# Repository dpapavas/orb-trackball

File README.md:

<!-- -*- coding: utf-8 -*- -->

# The Orb trackball

The Orb is a parametric trackball design, which uses BTUs as bearings to support
the ball for smooth, accurate, low-maintenance operation.  The design has the
form of a Scheme program, meant to be executed using the
[Gamma](https://github.com/dpapavas/gamma) computational geometry compiler, in
order to produce model files, that can then be used for fabrication.  This
allows substantial configurability, since parameters of the program can be
changed in order to alter the design, for instance to change the trackball
diameter, or adapt the design to different BTU part.

The Orb was created as a relatively complex application, that could be used to
drive the design of Gamma during the initial stages of development, but it works
pretty well and can be used in practice as a pointing device.  For a frew more
photos, see the [doc/](./doc) directory and see below for building instructions,
if you're interested in making one.

## Building an Orb

These instructions will be rather brief, as I do not expect many people to be
interested in making an Orb.  If you find that you are though and are unclear
about something, please open an issue on the Github project page, requesting
better documentation, making sure to mention the details you're unclear about.

The default configuration is made for a 55mm trackball (such as the one used in
the Kensington Expert Mouse) and the Ahcell D-6H BTU.  The PCB is mounted with
M3 screws, using threaded inserts with an M5-0.5x12 outer thread. If you decide
to use the same parts, you can use the pre-built STLs in [things/](./things/) and
skip the next section.

### Making design changes

To adapt the design for different parts (or make other customizations), you'll
first have to install Gamma. See its [project
page](https://github.com/dpapavas/gamma), for further instructions.  Once that
is accomplished, you're ready to compile the design.  The compilation process
creates lots of files, as it caches all intermediate non-trivial computations,
so it's best to carry it out in a separate directory, to keep things tidy.  (The
commands below assume you're starting out at the top-level directory of the Orb
sources.)

```bash
$ mkdir build
$ cd build
```

The design source (located in the [scheme/](./scheme/) directory) defines a set
of outputs, each of which can be compiled and written to a file in one of the
supported output formats.  To see the available outputs, you can use the
`-Woutputs` option, which enables warnings about unused outputs.  This will list
all of them, since we haven't selected any.

```bash
gamma -Woutputs ../scheme/trackball.scm
```

You can examine the sources to see what all of these outputs are about.  To
compile designs with the default configuration, we'll only need the `chassis` ,
`boot` and `cap` outputs, and we'll only need to concern ourselves with the
first for the time being.  We'll first build a draft design (`-Ddraft`), since
compilation in full resolution can take quite long and we just want to change a
few parameters and get an idea of the result.

```bash
gamma -Ddraft -o chassis.stl ../scheme/trackball.scm
```

The first compilation will typically take a while.  In draft mode, it should be
several minutes.  If you're worried that Gamma has frozen, you can use the
`--dump-operations=-` option, to convince yourself otherwise.  It takes so long,
because all calculations need to be carried out from scratch, but this will
typically only happen once.  Intermediate results are saved (which explains the
slew of `.o` or `.zo` files which now exist in your build directory) and future
recompilations will only recalculate the parts that have changed.  This helps
keep compilation times at relatively interactive levels most of the time.

To change the design to accept a different size ball, say a pool ball with a
diameter of 57.15mm, you only need to change the definition `ball-radius`
(setting it to `5715/200` [^1]) and recompile as before.  (You may note that
this compilation again takes some time.  That is because the change is quite
fundamental and requires changes and thus recalculation of most of the
geometry.)

Adapting the design to a different BTU part is also relatively straightforward.
For instance, if you want to use the `11MI-05-13` part (made by various
manufacturers) you need only to change `btu-radius` to `13/2` and
`btu-thread-length` to `15`.

After inspecting the draft result for any obvious defects, it's time to compile
the final part.  We work as before, but remove the `-Ddraft` option.

```bash
gamma -o chassis.stl ../scheme/trackball.scm
```

The part looks okay, but we can be more thorough.  The `interference` output takes
the intersection of the main chassis part with all mounted peripherals (PCB
board, BTUs, ball, etc.).  The result should ideally be empty, otherwise there
will be interference during assembly, but in practice, very small intersection
can be okay, depending on manufacturing tolerances and intended postprocessing of
the part.

We can also use the `-Dvertical=...` and `-Dhorizontal=...` options, to inspect
cross-sections of the part, for instance to make sure that wall thicknesses are
acceptable at critical points.  (See the comments in the sources for more
details.)

To get an idea of the assembled device, we just have to select the `assembly`
output and define some options to specify what to include in the assembly.

```bash
gamma -Dplace-ball -Dplace-board -Dplace-bearings -Dplace-caps -Dplace-boot -o assembly.stl ../scheme/trackball.scm
```

Finally, to make the bottom cover and keycaps, use the `boot` and `cap` outputs.

```bash
gamma -o boot.stl -o cap.stl ../scheme/trackball.scm
```

All this is not meant to give the idea that the design is infinitely flexible;
there are limits to the changes that can be carried out through simple
reparameterization.  These limits generally depend on the design, which can be
made to be more or less "generic", but small changes are usually okay.  After a
point though, changes in one part of the design may necessitate changes in other
parameters to ensure a defect-free result and still larger alterations can well
require changes to the design itself.

For some more tips on using Gamma, see the documentation for the [examples in
its project page](https://github.com/dpapavas/gamma/tree/master/examples).

## Fabrication

Once the parts have been compiled, they can be fabricated using a 3D printer, a
prototype fabrication service, or any other means at your disposal.  Note that,
depending on the manufacturing tolerance of the chosen method, you may need to
make minor changes to some design parameters to ensure perfect fit.
Alternatively, you can also postprocess the part instead.

The main chassis part and keycaps should be made in plastic (for instance using
TPU 3D printing filament) while the boot is meant to be flexible (TPU filament
or any rubber-like material should work fine).

## The controller board

The controller PCB was designed with [KiCad 6.0.7](https://kicad.org/)
and all relevant files are contained in the [kicad/](./kicad)
directory.

There are numerous fabrication services, where you can simply upload the KiCad
PCB file ([kicad/keyboard_mcu.kicad_pcb](./kicad/keyboard_mcu.kicad_pcb)) and
have a small number of PCBs fabricated and sent to you at a small price.  One
example, that is simple to use as it doesn't present you with a bewildering
array of choices, is [OSH Park](https://oshpark.com/).  Other services might
require so-called Gerber files, an industry standard which
[KiCad](https://kicad.org/) can generate.

The controller is designed around the Pixart PMW3389DM-T3QU optical sensor and
supports up to 5 buttons (or potentially 6, if some sort of matrix circuit is
used).  It should be adaptable to the PMW3360DM‐T2QU part, which is pin
compatible and uses the same lens, but note that some components will have to be
changed (for instance the current limiting resistor for the sensor LED).

### BOM

Apart from the PCBs, you'll also need the following parts:

| Component(s) | Part description | Part # |
| ------------ | ---------------- | ------ |
| C1, C14, C15, C18 (4 pcs, 10uF) | 10uF, 10%, X7R, 0603 | GRM188Z71A106KA73D |
| C2, C3 (2 pcs, 22p) | 15PF, 1%, C0G (NP0), 0603 | GRM1885C1H150FA01D |
| C4, C6, C7, C8, C10, C11, C12, C20 (8 pcs, 100nF) | 0.1uF, 10%, X7R, 0603 | EMK107B7104KA-T |
| C5, C9, C16, C17, C19 (5 pcs, 1uF) | 1uF, 10%, X7R, 0603 | EMK107B7105KA-T |
| C13 (1 pcs, 4.7uF 10V) | 4.7uF, 10V, 10%, X5R, 0603 | LMK107BJ475KA-T |
| J1 (1 pcs, USB_B_Micro) | USB Micro Type B connector | Wurth 629105150521 |
| J2, J3 (2 pcs, Conn) | 2.0mm pin header | Harwin M22-2530305 |
|  | 2.0mm female housing | Harwin M22-3010300 |
|  | 2.0mm crimp contact | Harwin M22-3040042 |
| R1, R2 (2 pcs, 22) | 22Ω, 1%, 0603 | CRCW060322R0FKEA |
| R3, R6 (2 pcs, 10K) | 10kΩ, 1%, 0603 | CRCW060310K0FKEA |
| R4 (1 pcs, 1k) | 1kΩ, 1%, 0603 | RCA06031K00FKEA |
| R5 (1 pcs, 13) | 13Ω, 1%, 0603 | CRCW060313R0FKEA |
| SW1 (1 pcs, SW_Push) | Tactile Switch SPST-NO | TL3305AF160QG |
| U1 (1 pcs ATmega32U4-AU) | AVR microcontroller | ATMEGA32U4-AU |
| U2 (1 pcs, LD39015M33R) | 150mA voltage regulator, 3.3V, SOT-23-5 | LD39015M33R |
| U3 (1 pcs, PMW3389-T3QU) | Optical sensor chip | PMW3389-T3QU |
| | Optical sensor lens | LM19‐LSI |
| U4 (1 pcs, TLV70019_SOT23-5) | 200mA voltage regulator, 1.9V, SOT-23-5 | TLV70019DDCR |
| Y1 (1 pcs, Crystal_GND24) | Four pin crystal, GND on pins 2 and 4 | ABM3B-8.000MHZ-10-1-U-T |

I've tried to select components with high availability, but you can treat the
part numbers given for the two-terminal chip resistor and capacitors as
suggestions.  Any part with the specifications listed in the part description
should do equally well.

In addition to the above, you'll need 5 Kailh CPG1350 CHOC low profile switches.
You can find these in many variations, but I would recommend low actuation force
parts, such as the "Red Rro" linear, or "Blue" clicky versions.  Apart from
ergonomic considerations, since the force of actuation is transmitted radially
to the chassis, it will tend to shift it around on the desk if it is too high.

Finally, I would advise not crimping your own wires unless you have the proper
equipment, prior experience and know you can do a good job.  The procedure can
be rather tedious and getting a proper result can be hard to impossible,
depending on the tools used.  You can get pre-crimped wires instead, but if you
do decide to crimp your own, get *plenty* of crimp terminals.

## Assembly

Assembly is simple in theory, but it can get tricky due to the confined work
space.  Start by inserting the threaded inserts.  The default design takes
inserts for M3 screws, with M5-0.5x12 outer thread, but it can be adapted to
other parts, if necessary (through the `board-insert-thread` and `boss-radius`
parameters).  See
[here](https://github.com/dpapavas/lagrange-keyboard/blob/master/BUILD.md#installing-the-threaded-inserts)
for installation instructions.

Continue by creating a common ground bus for the switches.  One way, is to make
it out of a single solid core wire with exposed loops at the proper intervals,
that can be soldered onto one terminal of each switch.  See
[here](https://github.com/dpapavas/lagrange-keyboard/blob/master/BUILD.md#rows)
for a potential technique.  The wire should have some slack, so that you can
pull the loops one at a time, far enough out of the switch hole, in order to
solder it to the switch, but not too much slack, or else the wire might
interfere with other parts.

Continue with the crimped and terminated wires for the switches.  These should
initially be of ample length, so that they can be threaded through the wiring
guides (the loops around the lens mating surface), around the lens and through
the switch holes (one pair through each hole, plus one common ground wire
connected to the ground bus), with the terminals at the place where the mating
headers on the board will end up.  Again, leave some slack, so that you can mate
the headers during assembly, but not too much, then cut the wires to length and
solder them, one at a time, to the switches and ground bus.

Carefully remove the Kapton tape protecting the optics of the sensor chip making
sure to hold the PCB with the chip face down, to avoid getting any dust on the
exposed optics, then quickly insert the lens (practice a bit before removing the
tape, to get the hang of the process).  Insert the PCB-lens assembly far enough
into the chassis to attach the headers, then insert it fully, making sure that
no wiring has been caught between the PCB or lens and the mating sites on the
chassis and fasten it using M3x12 button head screws.  Finally insert the boot
and you're done.

Unless the boot is manufactured using a high grip material, it is very much
recommended to coat the bottom with some silicone, or similar material, to
ensure sufficient traction and keep the device from sliding around.

## Firmware

Before building the firmware, have a look at the `./src/config.h` header and
make any necessary configuration changes.  You're probably going to have to set
the button pins, unless you happened to used the same pinout as I, but you can
also change the device-to-OS button mapping, optical resolution, sensitivities,
etc.

To build the firmware, you'll need the AVR GCC toolchain, which you can most
likely install through your system's package system.  Then building can be done
simply by:

```bash
$ cd src
$ make
```

Assuming nothing has gone wrong, connect the device to your computer and press
the reset switch.  You can then install the firmware with:

```bash
$ make install
```

## License

The Scheme code in [scheme/](./scheme), producing the Orb's designs, is
distributed under the [GNU Affero General Public License Version
3](./LICENSE.AGPL).

The firmware sources in [src/](./src), except for the portion in the
[src/LUFA/](./src/LUFA/) directory, as well as the controller PCB design
residing in [kicad/](./kicad/), is distributed under the [GNU General
Public License Version 3](./LICENSE.GPL).

For the sources in the [src/LUFA/](./src/LUFA/) see the [license
notice](./src/LUFA/License.txt) therein.

[^1]: You could also set it to `28.575` and it would work fine, but rational
      numbers should probably be preferred.  Gamma works with exact arithmetic
      on rational numbers (for the most part), so using floating point-input can
      result in needlessly "large" numbers.  For instance `28.575` is really
      `28.575000762939453125` in double precision floating point, with a
      rational representation of `8043147459506995/281474976710656`, instead of
      the much simpler `5715/200`.  (There's technically also some loss of
      precision, but this is generally down at the atomic scale, so we can
      probably ignore it).

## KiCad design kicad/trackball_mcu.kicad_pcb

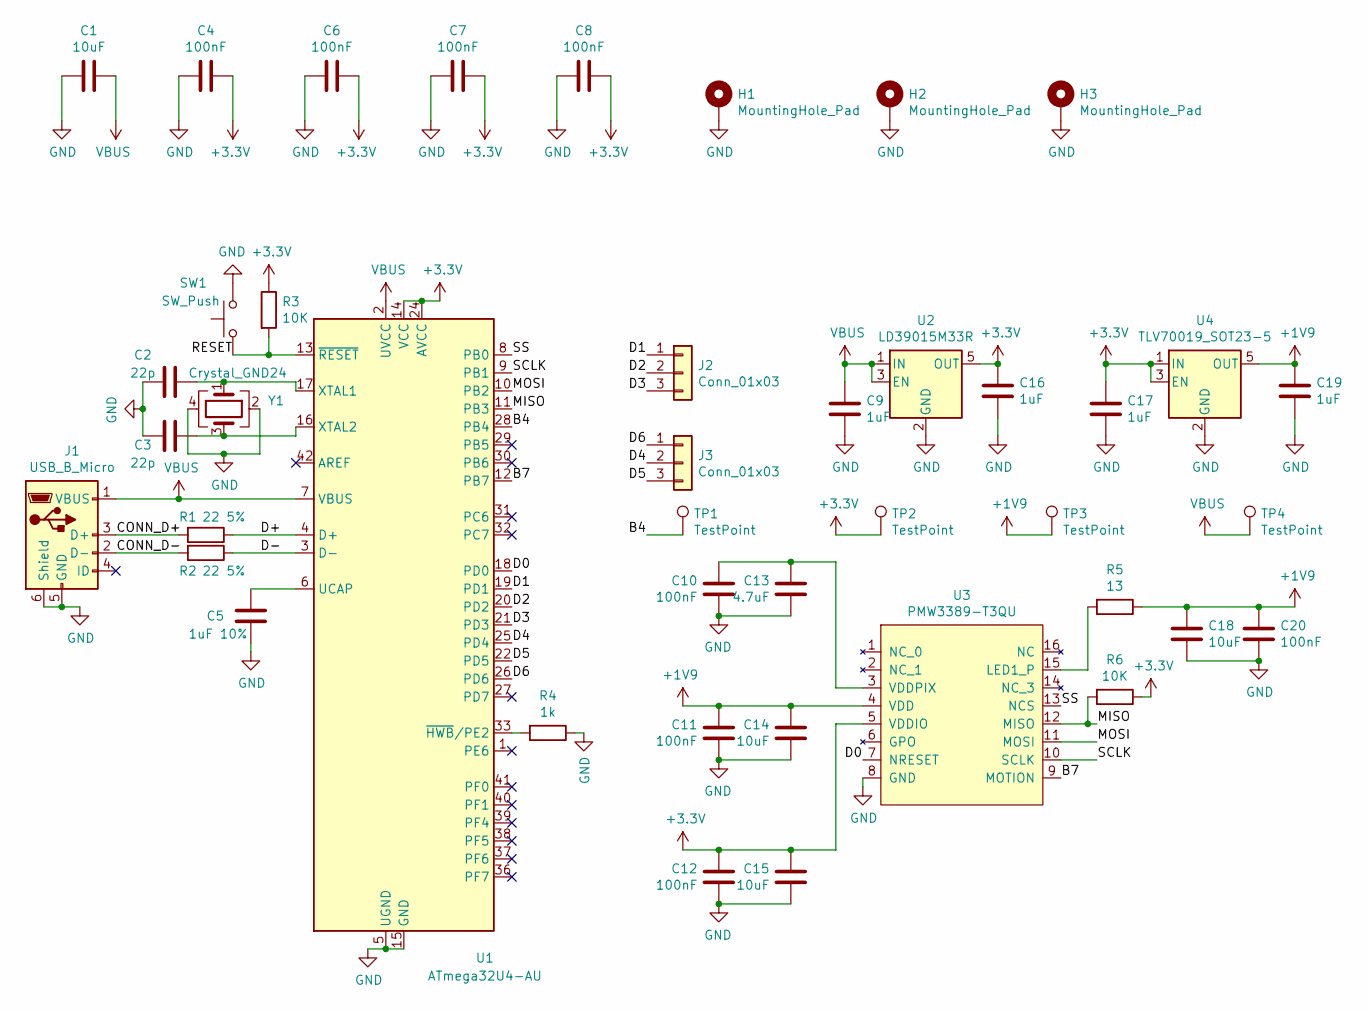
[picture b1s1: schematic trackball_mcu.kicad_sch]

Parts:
C1, C14, C15, C18: 10uF; C_0603_1608Metric_Pad1.08x0.95mm_HandSolder
C2, C3: 22p; C_0603_1608Metric_Pad1.08x0.95mm_HandSolder
C4, C6, C7, C8, C10, C11, C12, C20: 100nF; C_0603_1608Metric_Pad1.08x0.95mm_HandSolder
C5: 1uF 10%; C_0603_1608Metric_Pad1.08x0.95mm_HandSolder
C9, C16, C17, C19: 1uF; C_0603_1608Metric_Pad1.08x0.95mm_HandSolder
C13: 4.7uF; C_0603_1608Metric_Pad1.08x0.95mm_HandSolder
H1, H2, H3: MountingHole_Pad; MountingHole_2.7mm_M2.5_DIN965_Pad
J1: USB_B_Micro; USB_Micro-B_Wuerth_629105150521
J2, J3: Conn_01x03; Harwin_M22-203
R1, R2: 22 5%; R_0603_1608Metric_Pad0.98x0.95mm_HandSolder
R3, R6: 10K; R_0603_1608Metric_Pad0.98x0.95mm_HandSolder
R4: 1k; R_0603_1608Metric_Pad0.98x0.95mm_HandSolder
R5: 13; R_0603_1608Metric_Pad0.98x0.95mm_HandSolder
SW1: SW_Push; SW_SPST_TL3305B
TP1: TestPoint; TestPoint_THTPad_D1.0mm_Drill0.5mm
TP2, TP3, TP4: TestPoint; TestPoint_Pad_D1.0mm
U1: ATmega32U4-AU; TQFP-44_10x10mm_P0.8mm_Countoured
U2: LD39015M33R; SOT-23-5_HandSoldering
U3: PMW3389-T3QU; PMW3389DM-T3QU
U4: TLV70019_SOT23-5; SOT-23-5_HandSoldering
Y1: Crystal_GND24; Crystal_SMD_Abracon_ABM3B-4Pin_5.0x3.2mm_HandSoldering

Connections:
+1V9: C11.1, C14.1, C18.1, C19.1, C20.1, R5.1, TP3.1, U3.4 (VDD), U4.5 (OUT)
+3V3: C4.1, C6.1, C7.1, C8.1, C12.1, C15.1, C16.1, C17.1, R3.1, R6.1, TP2.1, U1.14 (VCC), U1.24 (AVCC), U1.34 (VCC), U1.44 (AVCC), U2.5 (OUT), U3.5 (VDDIO), U4.1 (IN), U4.3 (EN)
/B4: TP1.1, U1.28 (PB4)
/B7: U1.12 (PB7), U3.9 (MOTION)
/CONN_D+: J1.3 (D+), R1.2
/CONN_D-: J1.2 (D-), R2.2
/D0: U1.18 (PD0), U3.7 (NRESET)
/D1: J2.1, U1.19 (PD1)
/D2: J2.2, U1.20 (PD2)
/D3: J2.3, U1.21 (PD3)
/D4: J3.2, U1.25 (PD4)
/D5: J3.3, U1.22 (PD5)
/D6: J3.1, U1.26 (PD6)
/D+: R1.1, U1.4 (D+)
/D-: R2.1, U1.3 (D-)
/MISO: R6.2, U1.11 (PB3), U3.12 (MISO)
/MOSI: U1.10 (PB2), U3.11 (MOSI)
/RESET: R3.2, SW1.1, U1.13 (~RESET)
/SCLK: U1.9 (PB1), U3.10 (SCLK)
/SS: U1.8 (PB0), U3.13 (NCS)
GND: C1.2, C2.2, C3.2, C4.2, C5.2, C6.2, C7.2, C8.2, C9.2, C10.2, C11.2, C12.2, C13.1, C14.2, C15.2, C16.2, C17.2, C18.2, C19.2, C20.2, H1.1, H2.1, H3.1, J1.5 (GND), J1.6 (Shield), R4.1, SW1.2, U1.5 (UGND), U1.15 (GND), U1.23 (GND), U1.35 (GND), U1.43 (GND), U2.2 (GND), U3.8 (GND), U4.2 (GND), Y1.2, Y1.4
unnamed: C2.1, U1.17 (XTAL1), Y1.1
unnamed: C3.1, U1.16 (XTAL2), Y1.3
unnamed: C5.1, U1.6 (UCAP)
unnamed: C10.1, C13.2, U3.3 (VDDPIX)
unnamed: R4.2, U1.33 (~HWB/PE2)
unnamed: R5.2, U3.15 (LED1_P)
VBUS: C1.1, C9.1, J1.1 (VBUS), TP4.1, U1.2 (UVCC), U1.7 (VBUS), U2.1 (IN), U2.3 (EN)

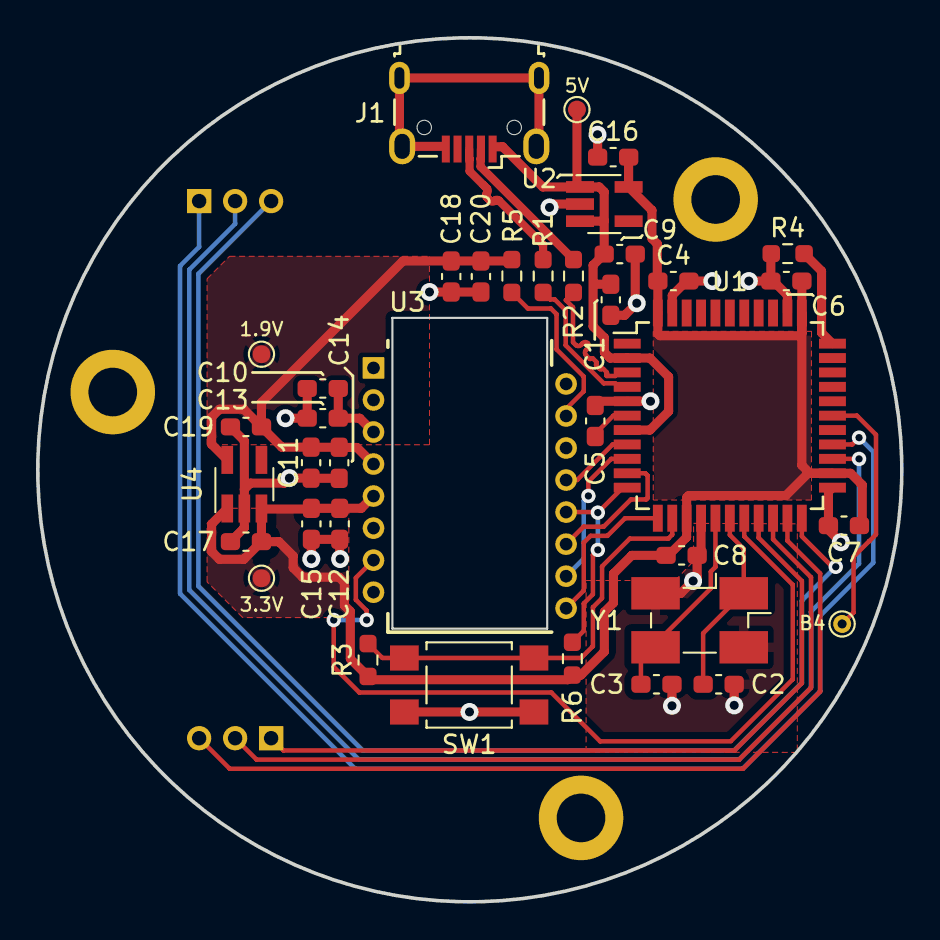
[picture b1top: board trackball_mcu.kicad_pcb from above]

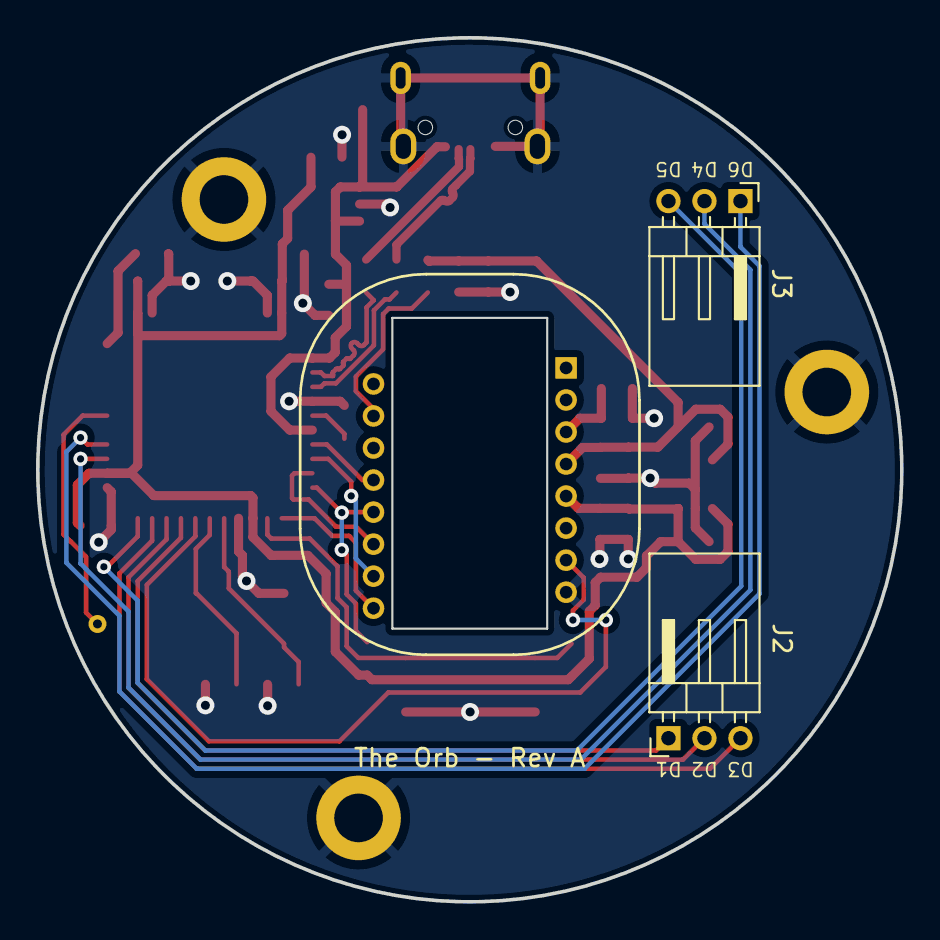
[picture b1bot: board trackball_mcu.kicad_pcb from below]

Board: 2 copper layers, 48.0 x 48.0 mm, 42 parts (2 on the bottom side), 28 nets.

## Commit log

2022-10-09 Import initial sources
2022-10-31 Add a mountable pedestal.
2023-10-02 Debounce the button switches.
